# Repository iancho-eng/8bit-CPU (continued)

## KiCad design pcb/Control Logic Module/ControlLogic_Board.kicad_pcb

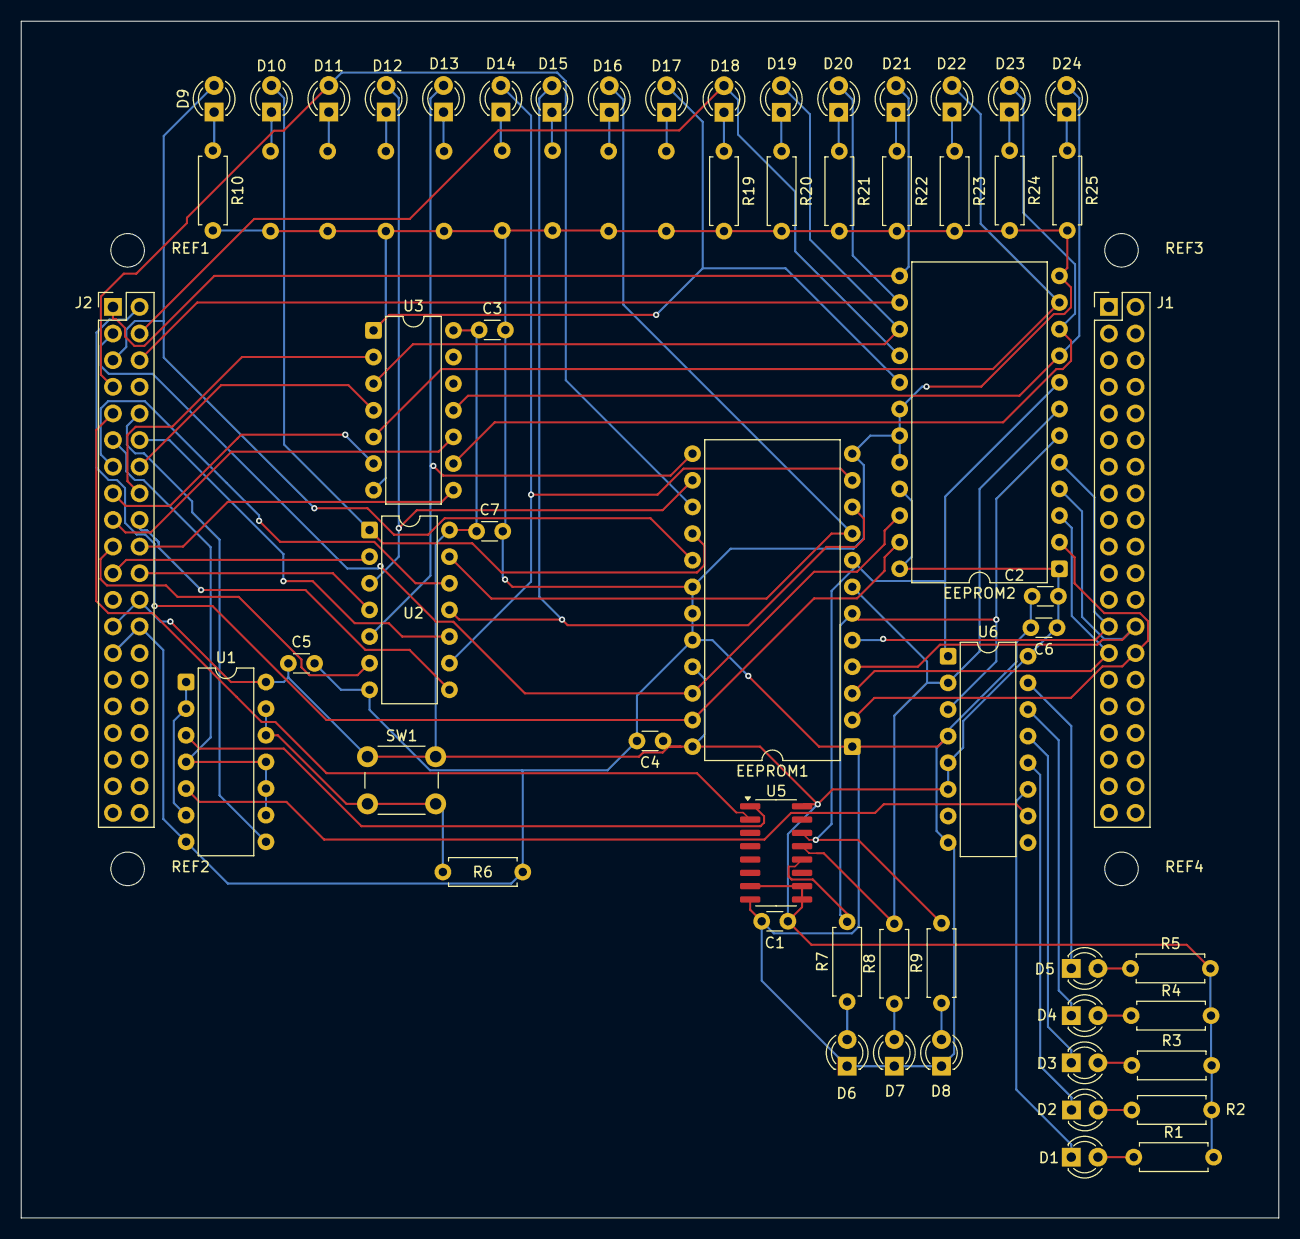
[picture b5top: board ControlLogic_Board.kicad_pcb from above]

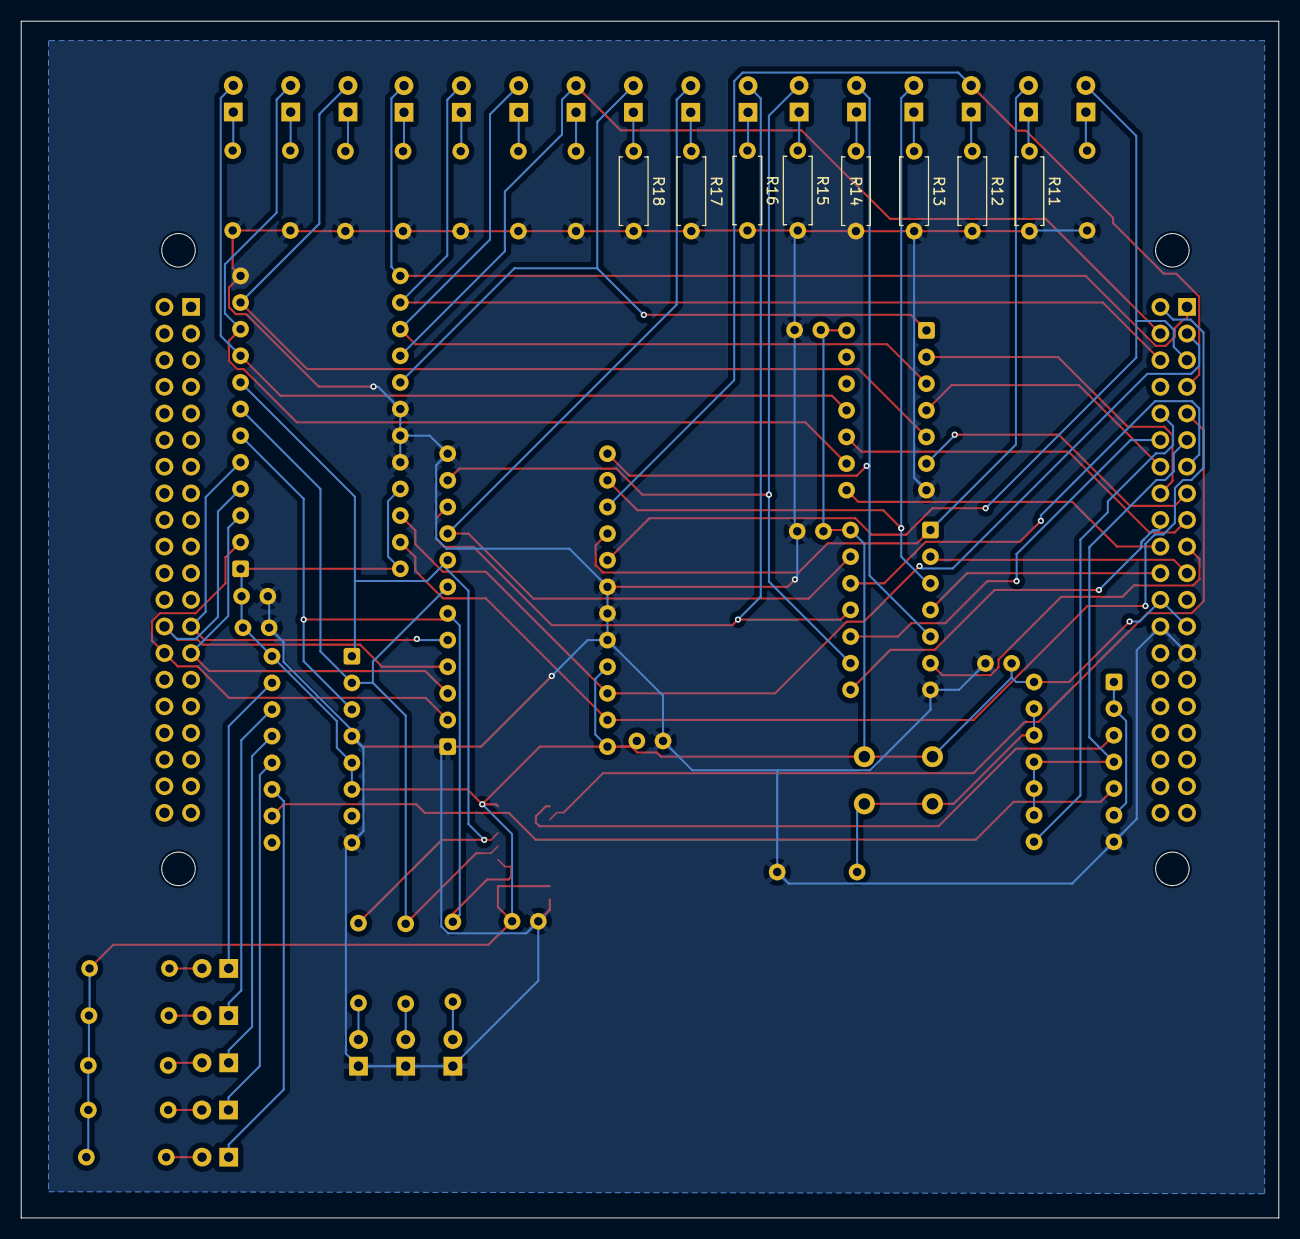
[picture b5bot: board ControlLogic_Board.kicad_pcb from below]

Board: 2 copper layers, 119.9 x 114.2 mm, 70 parts (8 on the bottom side), 74 nets.

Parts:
C1, C2, C3, C4, C5, C6, C7: 0.1uF; C_Disc_D3.0mm_W1.6mm_P2.50mm
D1, D2, D3, D4, D5: GREEN; LED_D3.0mm
D6, D7, D8: RED; LED_D3.0mm
D9, D10, D11, D12, D13, D14, D15, D16, D17, D18, D19, D20, D21, D22, D23, D24: BLUE; LED_D3.0mm
EEPROM1, EEPROM2: DIP-24_W15.24mm
J1, J2: Conn_02x20_Odd_Even; PinHeader_2x20_P2.54mm_Vertical
R1, R2, R3, R4, R5, R7, R8, R9, R10, R11, R12, R13, R14, R15, R16, R17, R18, R19, R20, R21, R22, R23, R24, R25: 220; R_Axial_DIN0207_L6.3mm_D2.5mm_P7.62mm_Horizontal
R6: 1K; R_Axial_DIN0207_L6.3mm_D2.5mm_P7.62mm_Horizontal
REF1, REF2, REF3, REF4: MountingHole_3.2mm_M3
SW1: SW_Push; SW_PUSH_6mm
U1: 74HCT00; DIP-14_W7.62mm
U2, U3: 74HCT04; DIP-14_W7.62mm
U5: 74HCT161D; SOIC-16_3.9x9.9mm_P1.27mm
U6: 74HCT138; DIP-16_W7.62mm

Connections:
/control logic/CE: D21.2 (A), EEPROM2.13 (D3), J2.1
/control logic/CF: EEPROM1.23 (A8), EEPROM2.23 (A8), J2.2
/control logic/CLR: J2.10, U1.8
/control logic/HLT: D9.2 (A), EEPROM1.17 (D7), J2.5
/control logic/IR_4: EEPROM1.5 (A3), EEPROM2.5 (A3), J1.25
/control logic/IR_5: EEPROM1.4 (A4), EEPROM2.4 (A4), J1.26
/control logic/IR_6: EEPROM1.3 (A5), EEPROM2.3 (A5), J1.27
/control logic/IR_7: EEPROM1.2 (A6), EEPROM2.2 (A6), J1.28
/control logic/OI: D20.2 (A), EEPROM2.14 (D4), J2.6
/control logic/RI: D11.2 (A), EEPROM1.15 (D5), J2.7
/control logic/SU: D18.2 (A), EEPROM2.16 (D6), J2.4
/control logic/ZF: EEPROM1.22 (A9), EEPROM2.22 (A9), J2.3
/control logic/~AI: J2.12, U2.10
/control logic/~AO: J2.13, U2.12
/control logic/~BI: J2.14, U3.4
/control logic/~CLK: J2.9, U5.2 (CP)
/control logic/~CLR: J2.11, U1.4, U1.9, U1.10, U1.11
/control logic/~CO: J2.15, U3.6
/control logic/~EO: J2.16, U3.2
/control logic/~FI: J2.17, U3.10
/control logic/~II: J2.18, U2.8
/control logic/~IO: J2.19, U2.6
/control logic/~J: J2.20, U3.8
/control logic/~MI: J2.21, U2.2
/control logic/~RO: J2.22, U2.4
GND: C1.2, C2.2, C3.2, C4.2, C5.2, C6.2, C7.2, D6.1 (K), D7.1 (K), D8.1 (K), EEPROM1.1 (A7), EEPROM1.12 (GND), EEPROM1.18 (~CE), EEPROM1.19 (A10), EEPROM1.20 (~OE), EEPROM2.12 (GND), EEPROM2.18 (~CE), EEPROM2.19 (A10), EEPROM2.20 (~OE), J2.26, J2.27, R6.2, R10.2, R11.2, R12.2, R13.2, R14.2, R15.2, R16.2, R17.2, R18.2, R19.2, R20.2, R21.2, R22.2, R23.2, R24.2, R25.2, U1.7 (GND), U2.7 (GND), U3.7 (GND), U5.8 (GND), U6.4 (~E0), U6.8 (GND)
unnamed: D1.2 (A), R1.1
unnamed: D1.1 (K), U6.11 (~Y4)
unnamed: D2.2 (A), R2.1
unnamed: D2.1 (K), U6.12 (~Y3)
unnamed: D3.2 (A), R3.1
unnamed: D3.1 (K), U6.13 (~Y2)
unnamed: D4.2 (A), R4.1
unnamed: D4.1 (K), U6.14 (~Y1)
unnamed: D5.2 (A), R5.1
unnamed: D5.1 (K), U6.15 (~Y0)
unnamed: D6.2 (A), R7.1
unnamed: D7.2 (A), R8.1
unnamed: D8.2 (A), R9.1
unnamed: D9.1 (K), R10.1
unnamed: D10.2 (A), EEPROM1.16 (D6), U2.1
unnamed: D10.1 (K), R11.1
unnamed: D11.1 (K), R12.1
unnamed: D12.2 (A), EEPROM1.14 (D4), U2.3
unnamed: D12.1 (K), R13.1
unnamed: D13.2 (A), EEPROM1.13 (D3), U2.5
unnamed: D13.1 (K), R14.1
unnamed: D14.2 (A), EEPROM1.11 (D2), U2.9
unnamed: D14.1 (K), R15.1
unnamed: D15.2 (A), EEPROM1.10 (D1), U2.11
unnamed: D15.1 (K), R16.1
unnamed: D16.2 (A), EEPROM1.9 (D0), U2.13
unnamed: D16.1 (K), R17.1
unnamed: D17.2 (A), EEPROM2.17 (D7), U3.1
unnamed: D17.1 (K), R18.1
unnamed: D18.1 (K), R19.1
unnamed: D19.2 (A), EEPROM2.15 (D5), U3.3
unnamed: D19.1 (K), R20.1
unnamed: D20.1 (K), R21.1
unnamed: D21.1 (K), R22.1
unnamed: D22.2 (A), EEPROM2.11 (D2), U3.5
unnamed: D22.1 (K), R23.1
unnamed: D23.2 (A), EEPROM2.10 (D1), U3.9
unnamed: D23.1 (K), R24.1
unnamed: D24.2 (A), EEPROM2.9 (D0), U3.11
unnamed: D24.1 (K), R25.1
unnamed: EEPROM1.8 (A0), EEPROM2.8 (A0), R9.2, U5.14 (Q0), U6.1 (A0)
unnamed: EEPROM1.7 (A1), EEPROM2.7 (A1), R8.2, U5.13 (Q1), U6.2 (A1)
unnamed: EEPROM1.6 (A2), EEPROM2.6 (A2), R7.2, U5.12 (Q2), U6.3 (A2)
unnamed: R6.1, SW1.2, U1.12, U1.13
unnamed: U1.1, U1.2, U1.6
unnamed: U1.3, U5.1 (~MR)
unnamed: U1.5, U6.10 (~Y5)
VCC: C1.1, C2.1, C3.1, C4.1, C5.1, C6.1, C7.1, EEPROM1.21 (~WE), EEPROM1.24 (VCC), EEPROM2.1 (A7), EEPROM2.21 (~WE), EEPROM2.24 (VCC), J2.24, J2.25, R1.2, R2.2, R3.2, R4.2, R5.2, SW1.1, U1.14 (VCC), U2.14 (VCC), U3.14 (VCC), U5.7 (CEP), U5.9 (~PE), U5.10 (CET), U5.16 (VCC), U6.5 (~E1), U6.6 (E2), U6.16 (VCC)

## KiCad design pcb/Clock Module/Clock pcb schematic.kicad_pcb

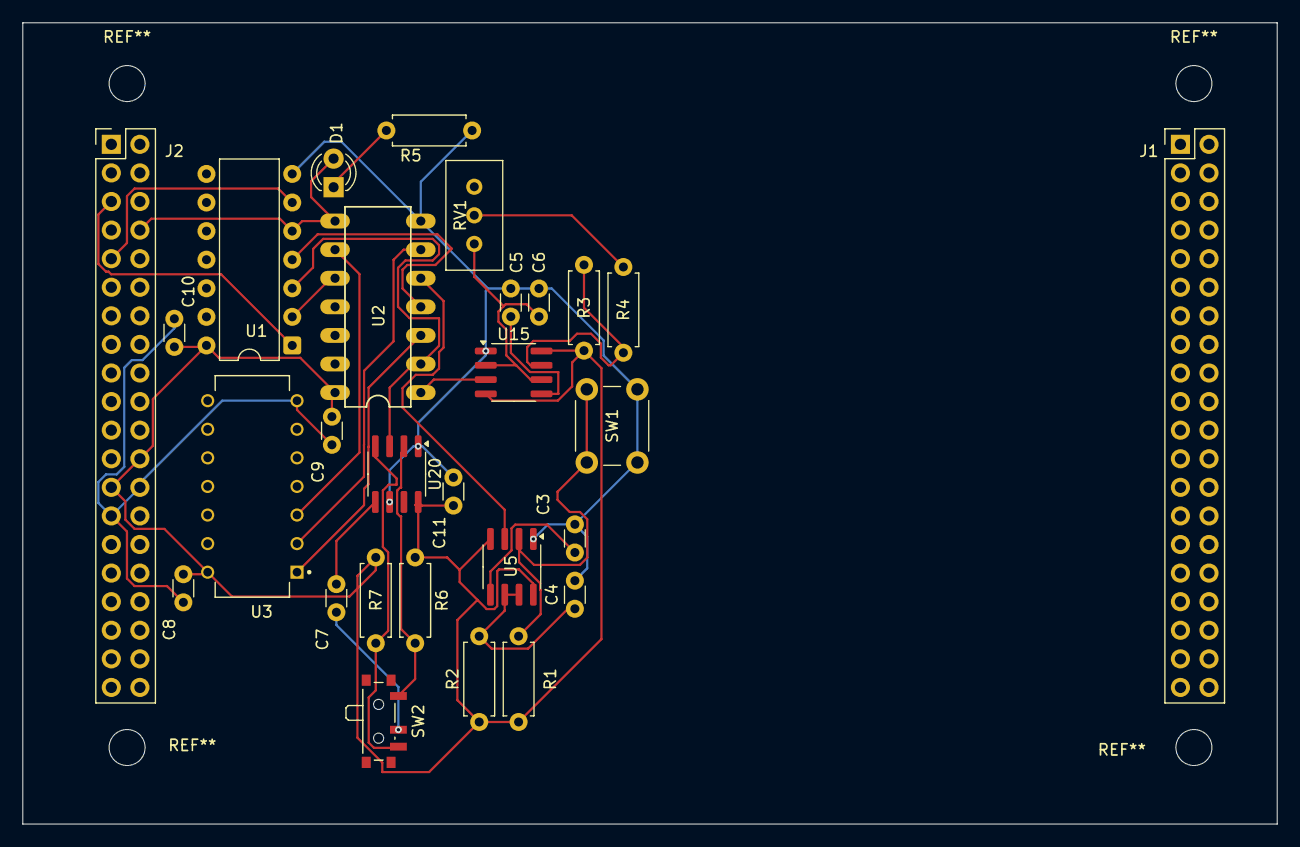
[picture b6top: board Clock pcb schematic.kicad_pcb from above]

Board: 2 copper layers, 111.5 x 71.2 mm, 28 parts (0 on the bottom side), 24 nets.

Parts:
C3, C5, C7, C8, C9, C10, C11: 0.01uF; C_Disc_D3.0mm_W1.6mm_P2.50mm
C4: 0.1uF; C_Disc_D3.0mm_W1.6mm_P2.50mm
C6: 1uF; C_Disc_D3.0mm_W1.6mm_P2.50mm
D1: BLUE; LED_D3.0mm
J1, J2: Conn_02x20_Odd_Even; PinHeader_2x20_P2.54mm_Vertical
R1, R3, R4, R6, R7: 1K; R_Axial_DIN0207_L6.3mm_D2.5mm_P7.62mm_Horizontal
R2: 1M; R_Axial_DIN0207_L6.3mm_D2.5mm_P7.62mm_Horizontal
R5: 220; R_Axial_DIN0207_L6.3mm_D2.5mm_P7.62mm_Horizontal
RV1: 1M; Potentiometer_Bourns_3296W_Vertical
SW1: SW_Push; SW_PUSH_6mm
SW2: SW_SPDT; SW_SPDT_PCM12
U1: 74HCT04; DIP-14_W7.62mm
U2: 74LS08
U3: 74LS32; DIP794W45P254L1969H508Q14
U5, U15, U20: LM555xM; SOIC-8_3.9x4.9mm_P1.27mm

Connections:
/Clock Module/CLK: D1.2 (A), J2.8, U1.5, U2.8
/Clock Module/HLT: J2.5, U1.1
/Clock Module/~CLK: J2.9, U1.6
GND: C3.2, C4.2, C5.2, C6.2, C7.2, C8.2, C9.2, C10.2, C11.1, J2.26, J2.27, R5.2, SW1.1, SW2.2 (B), U1.7 (GND), U2.7 (GND), U3.7 (GND), U5.1 (GND), U15.1 (GND), U20.1 (GND), U20.6 (THR)
unnamed: D1.1 (K), R5.1
unnamed: R4.1, RV1.2
unnamed: R6.2, SW2.1 (A), U20.2 (TR)
unnamed: R7.2, SW2.3 (C), U20.4 (R)
unnamed: U1.2, U2.10
unnamed: U1.4, U2.4
unnamed: U2.3, U3.1
unnamed: U2.6, U3.2
unnamed: U2.9, U3.3
unnamed: C3.1, U5.5 (CV)
unnamed: C4.1, R2.2, U5.6 (THR), U5.7 (DIS)
unnamed: U2.5, U5.3 (Q)
unnamed: R1.2, SW1.2, U5.2 (TR)
unnamed: C5.1, U15.5 (CV)
unnamed: R3.2, R4.2, U15.7 (DIS)
unnamed: U2.1, U15.3 (Q)
unnamed: C6.1, RV1.3, U15.2 (TR), U15.6 (THR)
unnamed: C7.1, U20.5 (CV)
unnamed: U1.3, U2.2, U20.3 (Q)
VCC: C8.1, C9.1, C10.1, C11.2, J2.24, J2.25, R1.1, R2.1, R3.1, R6.1, R7.1, U1.14 (VCC), U2.14 (VCC), U3.14 (VCC), U5.4 (R), U5.8 (VCC), U15.4 (R), U15.8 (VCC), U20.8 (VCC)

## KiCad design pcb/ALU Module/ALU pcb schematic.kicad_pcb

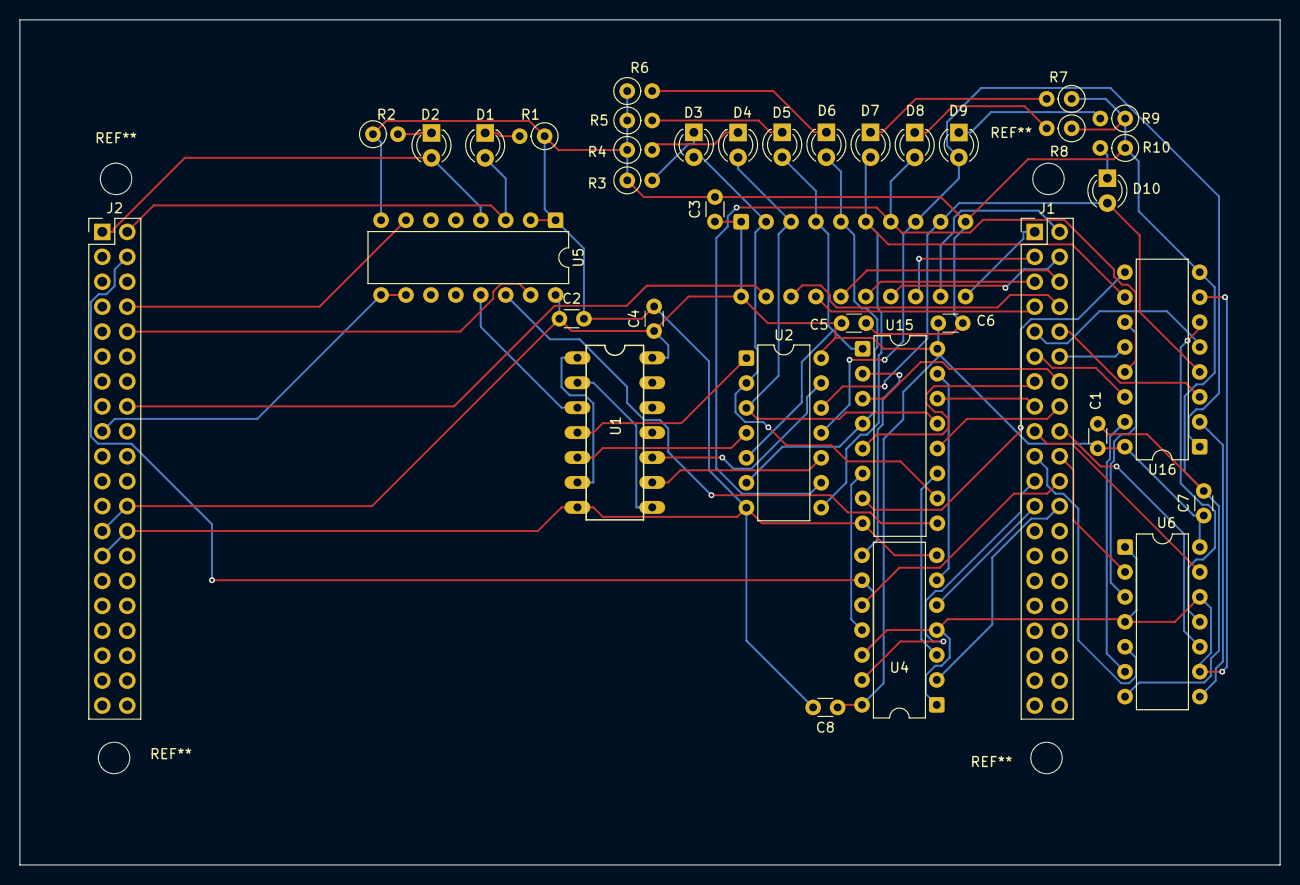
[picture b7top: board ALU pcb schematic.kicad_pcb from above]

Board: 2 copper layers, 128.4 x 86.1 mm, 38 parts (1 on the bottom side), 68 nets.

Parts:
C1, C2, C3, C4, C5, C6, C7, C8: 0.1u; C_Disc_D3.0mm_W1.6mm_P2.50mm
D1, D2: LED; LED_D3.0mm
D3, D4, D5, D6, D7, D8, D9, D10: RED; LED_D3.0mm
J1, J2: Conn_02x20_Odd_Even; PinHeader_2x20_P2.54mm_Vertical
R1, R3, R4, R5, R6, R7, R8, R9, R10: 220; R_Axial_DIN0207_L6.3mm_D2.5mm_P2.54mm_Vertical
R2: R; R_Axial_DIN0207_L6.3mm_D2.5mm_P2.54mm_Vertical
U1: 74LS08
U2: 74LS02; DIP-14_W7.62mm
U4, U6: 74LS86; DIP-14_W7.62mm
U5: 74HCT173; DIP-16_W7.62mm
U14: 74HCT245N; DIP-20_W7.62mm
U15, U16: 74LS283; DIP-16_W7.62mm

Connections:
/ALU module/A_0: J1.9, U16.5 (A1)
/ALU module/A_1: J1.10, U16.3 (A2)
/ALU module/A_2: J1.11, U16.14 (A3)
/ALU module/A_3: J1.12, U16.12 (A4)
/ALU module/A_4: J1.13, U15.5 (A1)
/ALU module/A_5: J1.14, U15.3 (A2)
/ALU module/A_6: J1.15, U15.14 (A3)
/ALU module/A_7: J1.16, U15.12 (A4)
/ALU module/BUS_0: J1.1, U14.11 (B7)
/ALU module/BUS_1: J1.2, U14.12 (B6)
/ALU module/BUS_2: J1.3, U14.13 (B5)
/ALU module/BUS_3: J1.4, U14.14 (B4)
/ALU module/BUS_4: J1.5, U14.15 (B3)
/ALU module/BUS_5: J1.6, U14.16 (B2)
/ALU module/BUS_6: J1.7, U14.17 (B1)
/ALU module/BUS_7: J1.8, U14.18 (B0)
/ALU module/B_0: J1.17, U6.13
/ALU module/B_1: J1.18, U6.10
/ALU module/B_2: J1.19, U6.5
/ALU module/B_3: J1.20, U6.2
/ALU module/B_4: J1.21, U4.13
/ALU module/B_5: J1.22, U4.10
/ALU module/B_6: J1.23, U4.5
/ALU module/B_7: J1.24, U4.2
/ALU module/CF: D1.2 (A), J2.2, U5.3 (Q0)
/ALU module/CLK: J2.8, U5.7 (Cp)
/ALU module/CLR: J2.10, U5.15 (Mr)
/ALU module/SU: J2.4, U4.1, U4.4, U4.9, U4.12, U6.1, U6.4, U6.9, U6.12, U16.7 (C0)
/ALU module/ZF: D2.2 (A), J2.1, U5.4 (Q1)
/ALU module/~EO: J2.16, U14.19 (~OE)
/ALU module/~FI: J2.17, U5.9 (E1), U5.10 (E2)
GND: C1.2, C2.2, C3.2, C4.2, C5.2, C6.2, C7.2, C8.2, J2.26, J2.27, R1.1, R2.1, R3.1, R4.1, R5.1, R6.1, R7.1, R8.1, R9.1, R10.1, U1.7 (GND), U2.7 (GND), U4.7 (GND), U5.1 (Oe1), U5.2 (Oe2), U5.8 (GND), U6.7 (GND), U14.10 (GND), U15.8 (GND), U16.8 (GND)
unnamed: D1.1 (K), R1.2
unnamed: D2.1 (K), R2.2
unnamed: D3.2 (A), U2.2, U14.2 (A0), U15.10 (S4)
unnamed: D3.1 (K), R3.2
unnamed: D4.2 (A), U2.3, U14.3 (A1), U15.13 (S3)
unnamed: D4.1 (K), R4.2
unnamed: D5.2 (A), U2.5, U14.4 (A2), U15.1 (S2)
unnamed: D5.1 (K), R5.2
unnamed: D6.2 (A), U2.6, U14.5 (A3), U15.4 (S1)
unnamed: D6.1 (K), R6.2
unnamed: D7.2 (A), U2.8, U14.6 (A4), U16.10 (S4)
unnamed: D7.1 (K), R7.2
unnamed: D8.2 (A), U2.9, U14.7 (A5), U16.13 (S3)
unnamed: D8.1 (K), R8.2
unnamed: D9.2 (A), U2.11, U14.8 (A6), U16.1 (S2)
unnamed: D9.1 (K), R9.2
unnamed: D10.2 (A), U2.12, U14.9 (A7), U16.4 (S1)
unnamed: D10.1 (K), R10.2
unnamed: U1.1, U1.6
unnamed: U1.2, U1.8
unnamed: U1.4, U2.1
unnamed: U1.5, U2.4
unnamed: U1.9, U2.10
unnamed: U1.10, U2.13
unnamed: U1.3, U5.13 (D1)
unnamed: U4.11, U15.6 (B1)
unnamed: U4.8, U15.2 (B2)
unnamed: U4.6, U15.15 (B3)
unnamed: U4.3, U15.11 (B4)
unnamed: U15.7 (C0), U16.9 (C4)
unnamed: U5.14 (D0), U15.9 (C4)
unnamed: U6.11, U16.6 (B1)
unnamed: U6.8, U16.2 (B2)
unnamed: U6.6, U16.15 (B3)
unnamed: U6.3, U16.11 (B4)
VCC: C1.1, C2.1, C3.1, C4.1, C5.1, C6.1, C7.1, C8.1, J2.24, J2.25, U1.14 (VCC), U2.14 (VCC), U4.14 (VCC), U5.16 (VCC), U6.14 (VCC), U14.1 (DIR), U14.20 (VCC), U15.16 (VCC), U16.16 (VCC)

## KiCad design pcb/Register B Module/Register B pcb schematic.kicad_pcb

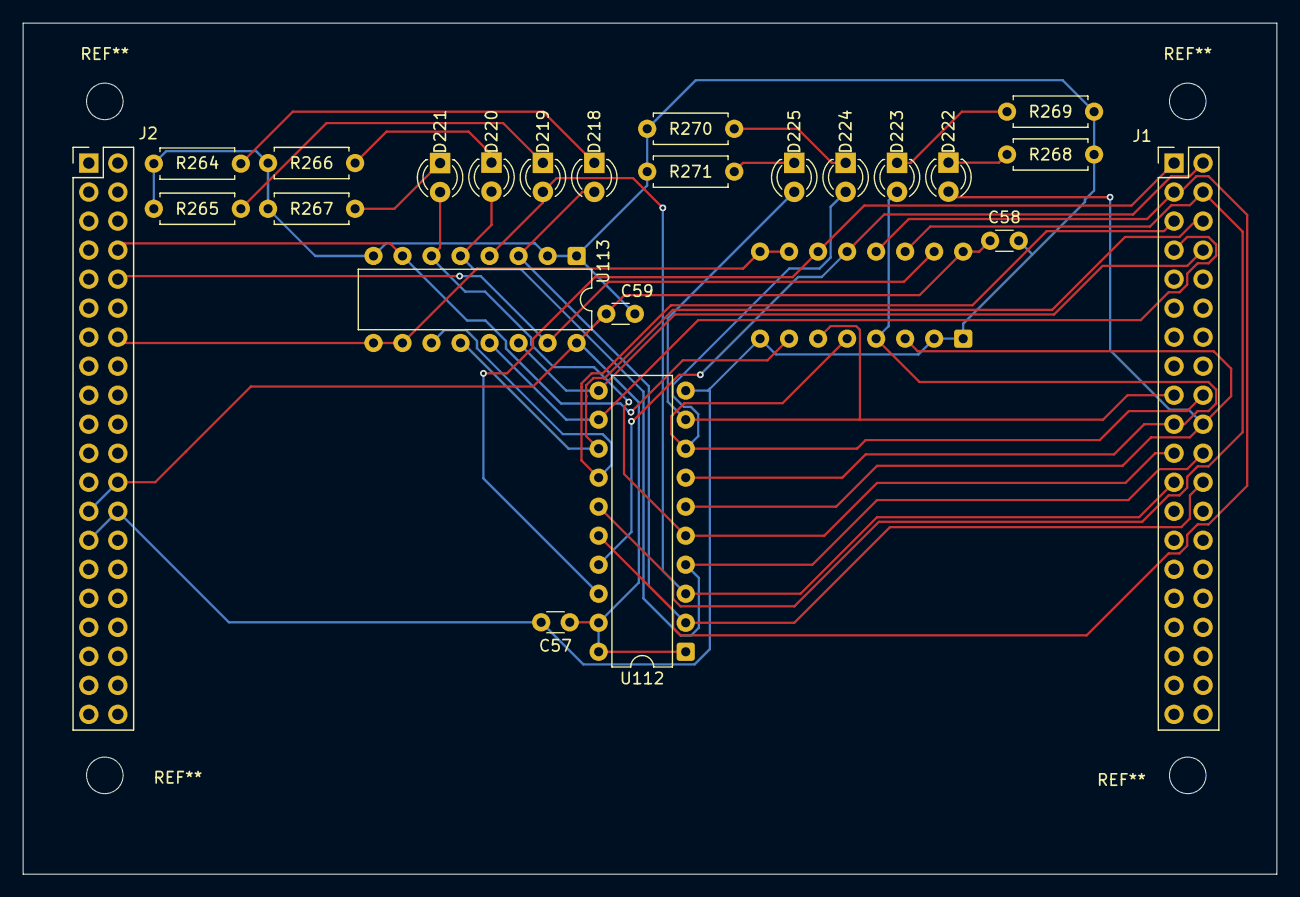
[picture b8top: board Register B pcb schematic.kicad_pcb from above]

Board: 2 copper layers, 109.8 x 74.5 mm, 24 parts (1 on the bottom side), 29 nets.

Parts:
C57, C58, C59: 0.1uF; C_Disc_D3.0mm_W1.6mm_P2.50mm
D218, D219, D220, D221, D222, D223, D224, D225: RED; LED_D3.0mm
J1, J2: Conn_02x20_Odd_Even; PinHeader_2x20_P2.54mm_Vertical
R264, R265, R266, R267, R268, R269, R270, R271: 220; R_Axial_DIN0207_L6.3mm_D2.5mm_P7.62mm_Horizontal
U112: 74HCT245N; DIP-20_W7.62mm
U113, U114: 74HCT173; DIP-16_W7.62mm

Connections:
/Register B Module/BUS_0: J1.1, U112.18 (B0), U114.11 (D3)
/Register B Module/BUS_1: J1.2, U112.17 (B1), U114.12 (D2)
/Register B Module/BUS_2: J1.3, U112.16 (B2), U114.13 (D1)
/Register B Module/BUS_3: J1.4, U112.15 (B3), U114.14 (D0)
/Register B Module/BUS_4: J1.5, U112.14 (B4), U113.11 (D3)
/Register B Module/BUS_5: J1.6, U112.13 (B5), U113.12 (D2)
/Register B Module/BUS_6: J1.7, U112.12 (B6), U113.13 (D1)
/Register B Module/BUS_7: J1.8, U112.11 (B7), U113.14 (D0)
/Register B Module/B_0: D225.2 (A), J1.17, U112.9 (A7), U114.6 (Q3)
/Register B Module/B_1: D224.2 (A), J1.18, U112.8 (A6), U114.5 (Q2)
/Register B Module/B_2: D223.2 (A), J1.19, U112.7 (A5), U114.4 (Q1)
/Register B Module/B_3: D222.2 (A), J1.20, U112.6 (A4), U114.3 (Q0)
/Register B Module/B_4: D221.2 (A), J1.21, U112.5 (A3), U113.6 (Q3)
/Register B Module/B_5: D220.2 (A), J1.22, U112.4 (A2), U113.5 (Q2)
/Register B Module/B_6: D219.2 (A), J1.23, U112.3 (A1), U113.4 (Q1)
/Register B Module/B_7: D218.2 (A), J1.24, U112.2 (A0), U113.3 (Q0)
/Register B Module/CLK: J2.8, U113.7 (Cp), U114.7 (Cp)
/Register B Module/CLR: J2.10, U113.15 (Mr), U114.15 (Mr)
/Register B Module/~BI: J2.14, U113.9 (E1), U113.10 (E2), U114.9 (E1), U114.10 (E2)
GND: C57.2, C58.2, C59.2, J2.26, J2.27, R264.2, R265.2, R266.2, R267.2, R268.2, R269.2, R270.2, R271.2, U112.10 (GND), U113.1 (Oe1), U113.2 (Oe2), U113.8 (GND), U114.1 (Oe1), U114.2 (Oe2), U114.8 (GND)
unnamed: D218.1 (K), R264.1
unnamed: D219.1 (K), R265.1
unnamed: D220.1 (K), R266.1
unnamed: D221.1 (K), R267.1
unnamed: D222.1 (K), R268.1
unnamed: D223.1 (K), R269.1
unnamed: D224.1 (K), R270.1
unnamed: D225.1 (K), R271.1
VCC: C57.1, C58.1, C59.1, J2.24, J2.25, U112.1 (DIR), U112.19 (~OE), U112.20 (VCC), U113.16 (VCC), U114.16 (VCC)

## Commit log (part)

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2025-09-06 Rename schematics.md to schematics.png
2025-09-06 Rename 8-bit CPU block diagram (1).png to 8-bit CPU block diagram.png
2025-09-07 Rename 8-bit CPU project report (1).pdf to 8-bit CPU documentation.pdf
2026-03-19 Revise README with detailed project description
    Expanded project overview, features, and architecture details in README.
